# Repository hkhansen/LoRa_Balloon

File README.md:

# LoRa_Balloon
This repository contains all files used for creating and developing the Long Range Tracker balloon tracker.
These trackers are cuurently used by DTU Space for tracking stratospheric balloons carrying experiments.

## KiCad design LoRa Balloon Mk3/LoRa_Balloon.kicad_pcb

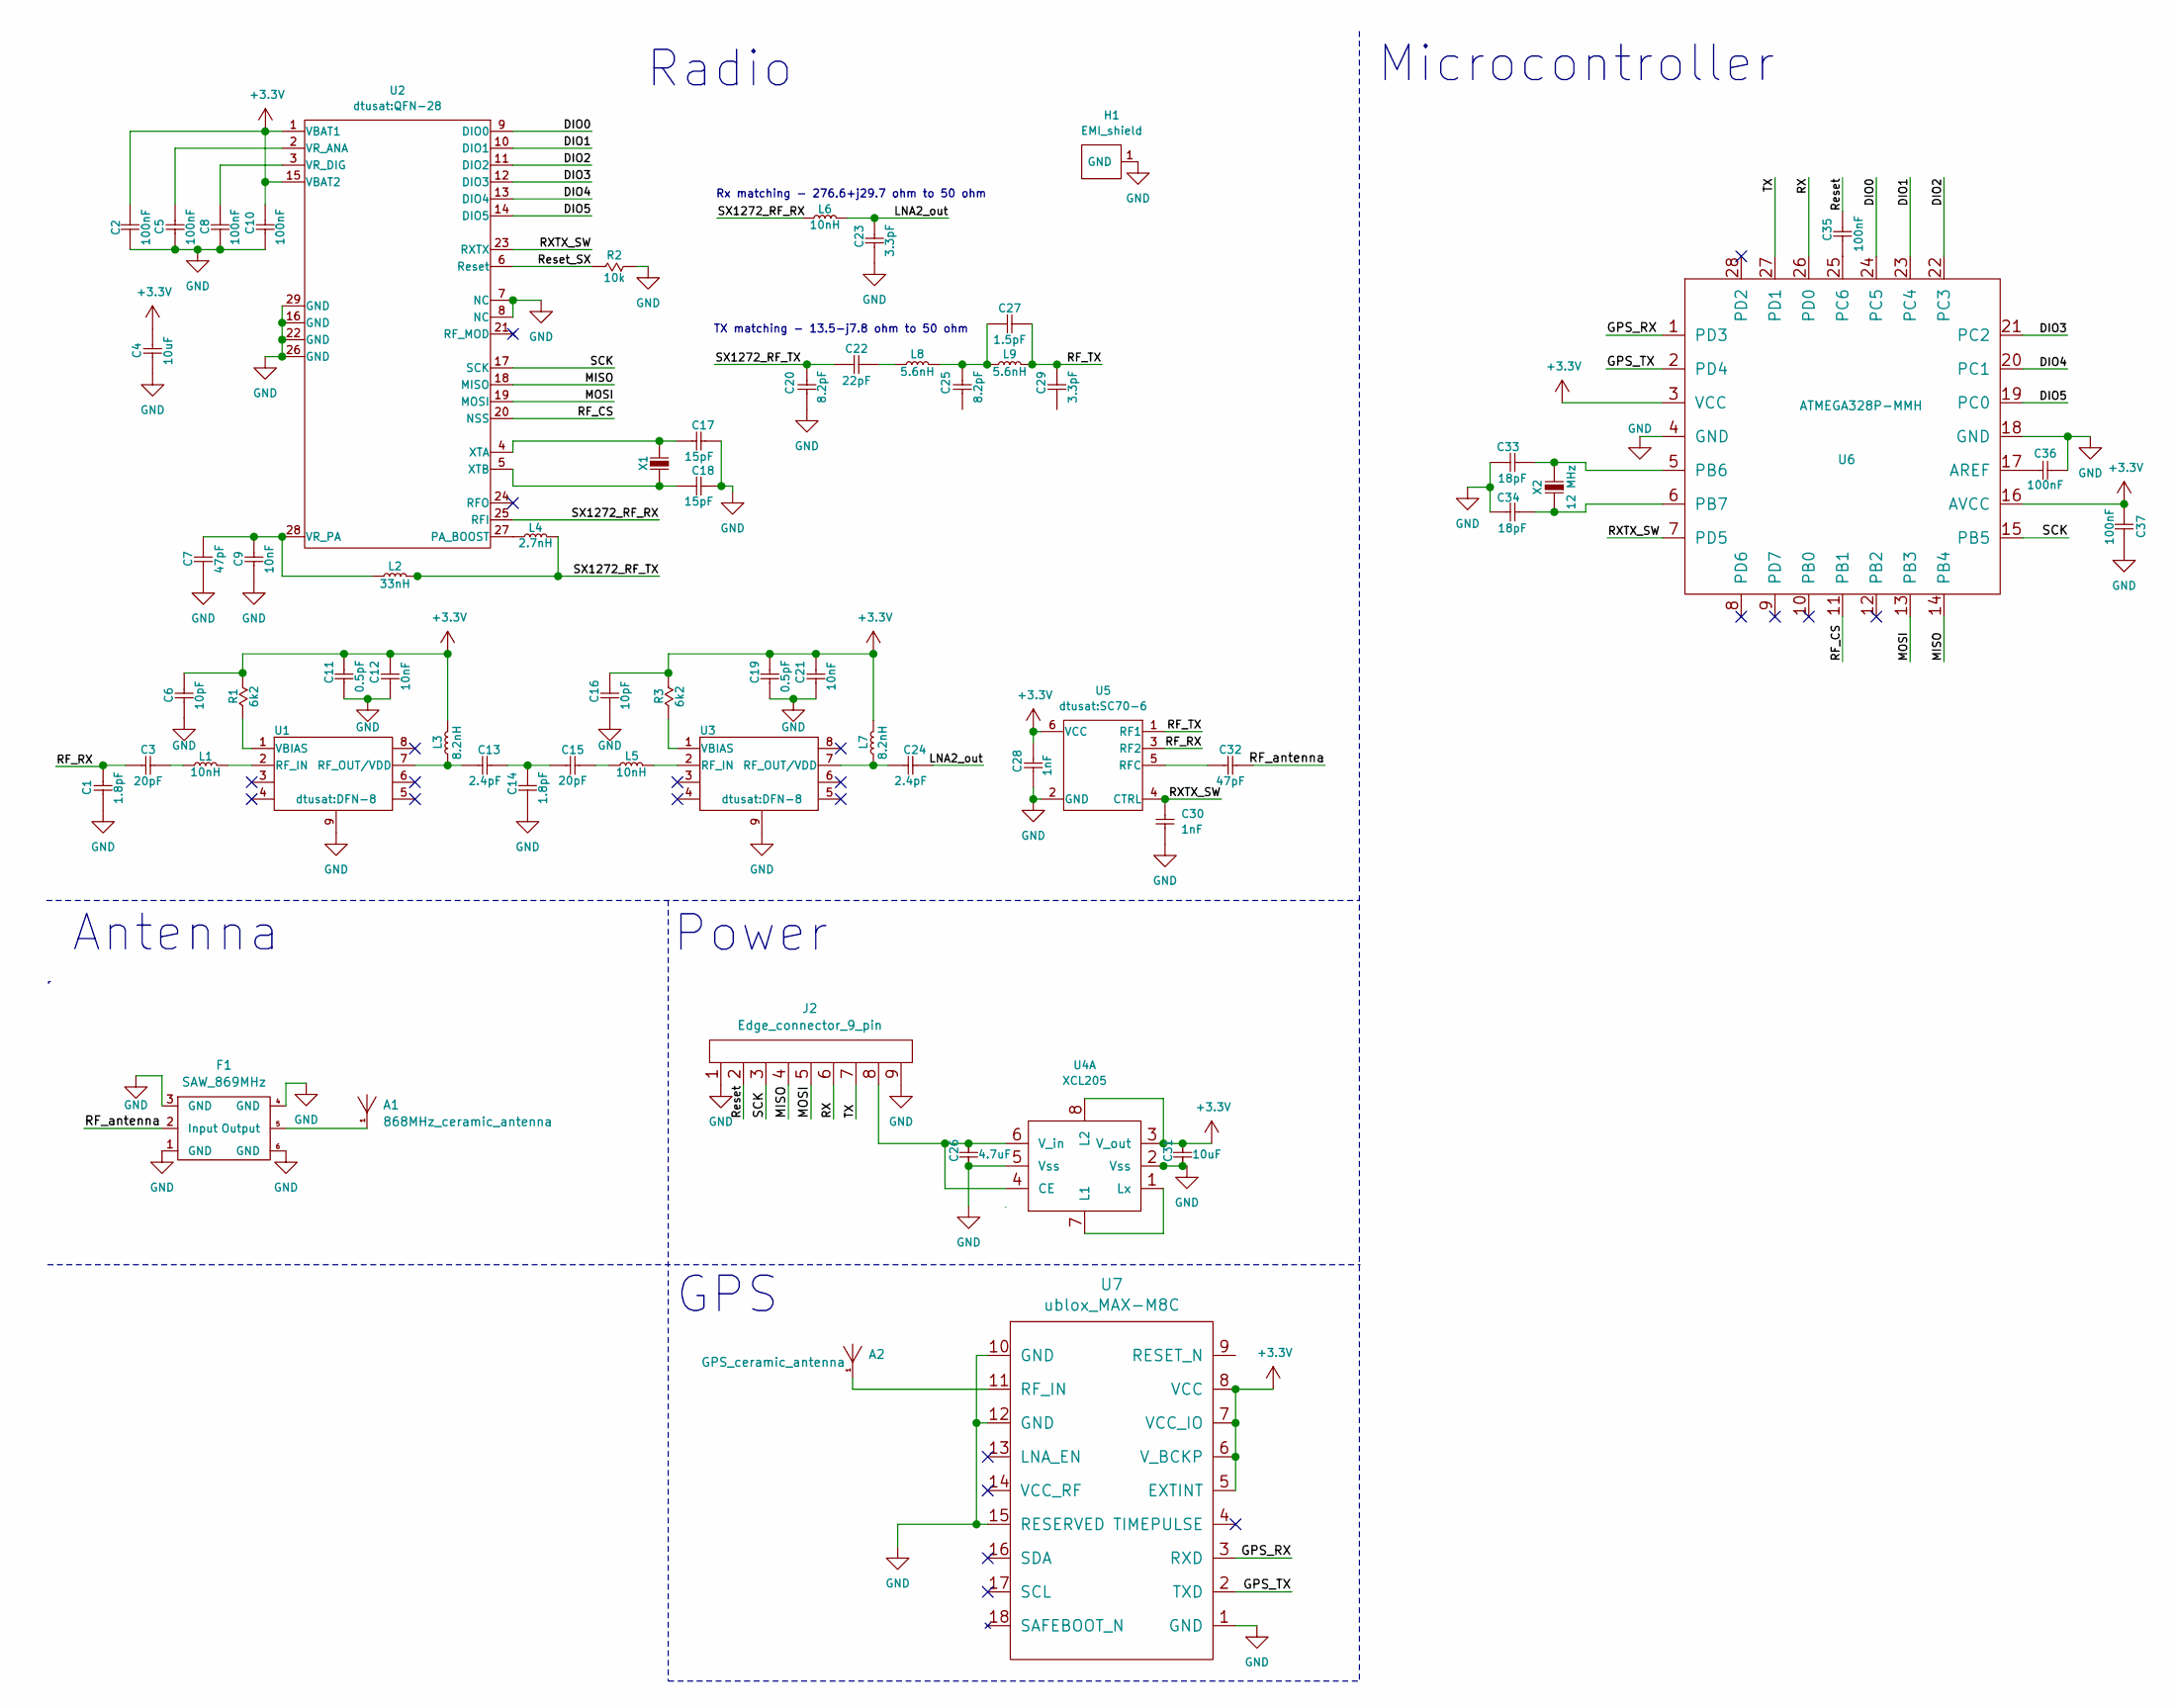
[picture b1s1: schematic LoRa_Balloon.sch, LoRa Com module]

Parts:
A1: 868MHz_ceramic_antenna; Antenna_868MHz
A2: GPS_ceramic_antenna; Ceramic_Antenna
C1, C14: C_0402_1.8pF_CID2085; C0402; Tolerance 0.1pF
C2, C5, C8, C10: C_0402_100nF_CID2080; C0402; Tolerance 10%
C3, C15: C_0402_20pF_CID2086; C0402; Tolerance 5%
C4: C_0805_10uF_CID2079; C0805; Tolerance 10%
C6, C16: C_0402_10pF_CID2089; C0402; Tolerance 1%
C7, C32: C_0402_47pF_CID2081; C0402; Tolerance 5%
C9, C12, C21: C_0402_10nF_CID2082; C0402; Tolerance 10%
C11, C19: C_0402_0.5pF_CID2091; C0402; Tolerance 0.1pF
C13, C24: C_0402_2.4pF_CID2093; C0402; Tolerance 0.05pF
C17, C18: C_0402_15pF_CID2083; C0402; Tolerance 1%
C20, C25: C_0402_8.2pF_CID2088; C0402; Tolerance 0.25pF
C22: C_0402_22pF_CID2090; C0402; Tolerance 5%
C23, C29: C_0402_3.3pF_CID2084; C0402; Tolerance 0.25pF
C26, C31: C_1206_4.7uF_CID2013_small; C0603
C27: C_0402_1.5pF_CID2087; C0402; Tolerance 0.1pF
C28, C30: C_0402_1nF_CID2092; C0402; Tolerance 1%
C33, C34: C_0603_18pF_CID2019; C0402; Tolerance 5%
C35, C36, C37: C_0402_100nF_CID2072; C0402; Tolerance 10%
F1: SAW_869MHz
H1: EMI_shield; BMI-S-203-F_EMI_shield
J2: Edge_connector_9_pin
L1, L5, L6: L_0402_10nH_CID3037; L0402; Tolerance 2%
L2: L_0402_33nH_CID3034; L0402; Tolerance 2nH
L3, L7: L_0402_8.2nH_CID3038; L0402; Tolerance 2%
L4: L_0402_2.7nH_CID3035; L0402; Tolerance 0.1nH
L8, L9: L_0402_5.6nH_CID3036; L0402; Tolerance 0.2nH
R1, R3: R_0402_6k2_CID1104; R0402; Tolerance 1%
R2: R_0402_10k_CID1101; R0402; Tolerance 1%
U1, U3: SKY67013-396LF_CID141; DFN-8
U2: SX1272IMLTRICT-ND_CID104; QFN-28
U4: XCL205
U5: PE4259_CID105; SC70-6
U6: ATMEGA328P-MMH; ATMega328P_MMH
U7: ublox_MAX-M8C
X1: X1E0000210162_CID142; TSX-3225
X2: 7A-12.000MAAJ-T_CID117; TXC14.3

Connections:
+3V3: C4.1, C6.1, C11.1, C12.1, C16.1, C19.1, C21.1, C28.1, C31.1, C37.2, L3.1, L7.1, R1.1, R3.1, U4.3 (V_out), U4.8 (L2), U5.6 (VCC), U6.3 (VCC), U6.16 (AVCC), U7.5 (EXTINT), U7.6 (V_BCKP), U7.7 (VCC_IO), U7.8 (VCC)
/DIO0: U2.9 (DIO0), U6.24 (PC5)
/DIO1: U2.10 (DIO1), U6.23 (PC4)
/DIO2: U2.11 (DIO2), U6.22 (PC3)
/DIO3: U2.12 (DIO3), U6.21 (PC2)
/DIO4: U2.13 (DIO4), U6.20 (PC1)
/DIO5: U2.14 (DIO5), U6.19 (PC0)
/GPS_RX: U6.1 (PD3), U7.3 (RXD)
/GPS_TX: U6.2 (PD4), U7.2 (TXD)
/LNA2_out: C23.1, C24.1, L6.1
/MISO: J2.4, U2.18 (MISO), U6.14 (PB4)
/MOSI: J2.5, U2.19 (MOSI), U6.13 (PB3)
/RF_CS: U2.20 (NSS), U6.11 (PB1)
/RF_RX: C1.1, C3.2, U5.3 (RF2)
/RF_TX: C27.1, C29.1, L9.1, U5.1 (RF1)
/RF_antenna: C32.1, F1.2 (Input)
/RX: J2.6, U6.26 (PD0)
/RXTX_SW: C30.1, U2.23 (RXTX), U5.4 (CTRL), U6.7 (PD5)
/Reset: C35.1, J2.2
/Reset_SX: R2.2, U2.6 (Reset)
/SCK: J2.3, U2.17 (SCK), U6.15 (PB5)
/SX1272_RF_RX: L6.2, U2.25 (RFI)
/SX1272_RF_TX: C20.1, C22.2, L2.1, L4.1
/TX: J2.7, U6.27 (PD1)
GND: C1.2, C2.2, C4.2, C5.2, C6.2, C7.2, C8.2, C9.2, C10.2, C11.2, C12.2, C14.2, C16.2, C17.1, C18.1, C19.2, C20.2, C21.2, C23.2, C26.2, C28.2, C30.2, C31.2, C33.1, C34.1, C36.1, C37.1, F1.1 (GND), F1.3 (GND), F1.4 (GND), F1.6 (GND), H1.1, J2.1, J2.9, R2.1, U1.9, U2.7 (NC), U2.8 (NC), U2.16 (GND), U2.22 (GND), U2.26 (GND), U2.29 (GND), U3.9, U4.2 (Vss), U4.5 (Vss), U4.GND, U5.2 (GND), U6.4 (GND), U6.18 (GND), U7.1 (GND), U7.10 (GND), U7.12 (GND), U7.15 (RESERVED)
unnamed: A1.1, F1.5 (Output)
unnamed: A2.1, U7.11 (RF_IN)
unnamed: C3.1, L1.2
unnamed: C5.1, U2.2 (VR_ANA)
unnamed: C7.1, C9.1, L2.2, U2.28 (VR_PA)
unnamed: C8.1, U2.3 (VR_DIG)
unnamed: C2.1, C10.1, U2.1 (VBAT1), U2.15 (VBAT2)
unnamed: C13.1, C14.1, C15.2
unnamed: C13.2, L3.2, U1.7 (RF_OUT/VDD)
unnamed: C15.1, L5.2
unnamed: C17.2, U2.4 (XTA), X1.1
unnamed: C18.2, U2.5 (XTB), X1.3
unnamed: C22.1, L8.2
unnamed: C24.2, L7.2, U3.7 (RF_OUT/VDD)
unnamed: C25.1, C27.2, L8.1, L9.2
unnamed: C26.1, J2.8, U4.4 (CE), U4.6 (V_in)
unnamed: C32.2, U5.5 (RFC)
unnamed: C33.2, U6.5 (PB6), X2.2
unnamed: C34.2, U6.6 (PB7), X2.1
unnamed: C35.2, U6.25 (PC6)
unnamed: C36.2, U6.17 (AREF)
unnamed: L1.1, U1.2 (RF_IN)
unnamed: L4.2, U2.27 (PA_BOOST)
unnamed: L5.1, U3.2 (RF_IN)
unnamed: R1.2, U1.1 (VBIAS)
unnamed: R3.2, U3.1 (VBIAS)
unnamed: U4.1 (Lx), U4.7 (L1)

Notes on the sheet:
Rx matching - 276.6+j29.7 ohm to 50 ohm
TX matching - 13.5-j7.8 ohm to 50 ohm
Radio
Antenna
Power
Microcontroller
GPS

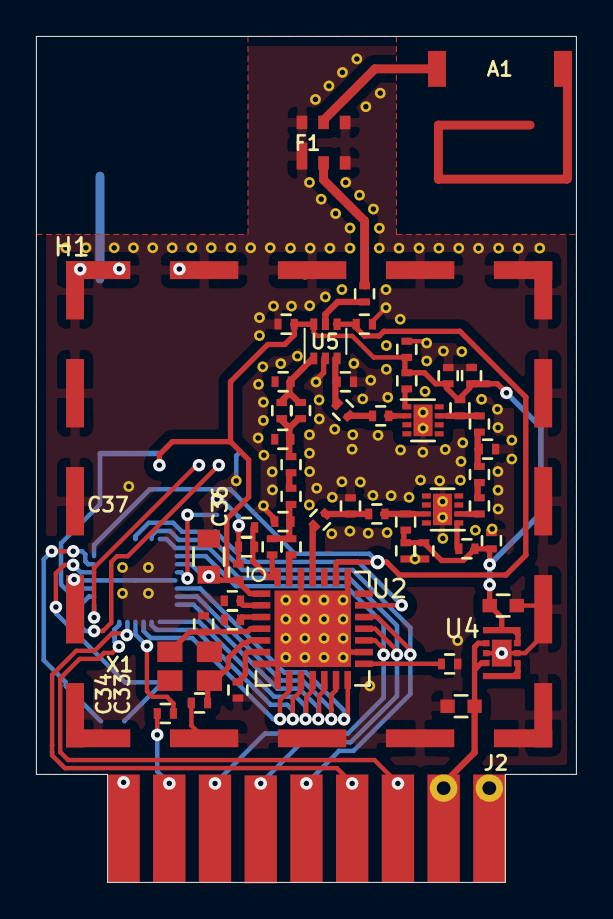
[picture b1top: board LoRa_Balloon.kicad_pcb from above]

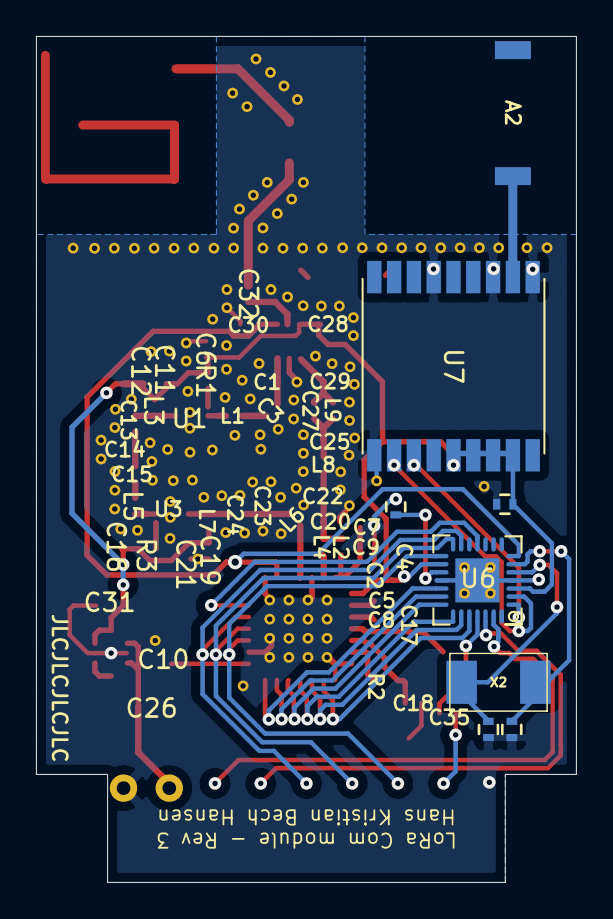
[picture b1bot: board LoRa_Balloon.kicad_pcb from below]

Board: 2 copper layers, 30.0 x 47.0 mm, 63 parts (8 on the bottom side), 52 nets.

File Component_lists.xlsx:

Componet references - LoRa_Balloon
Capacitors
REF | Value | Unit | CID
C1, C14 | 1.8 | pF | 2085
C11, C19 | 0.5 | pF | 2091
C13, C24 | 2.4 | pF | 2093
C17, C18 | 15 | pF | 2083
C2, C5, C8, C10, C33, C34, C35, C36 | 100 | nF | 2080
C20, C25 | 8.1999999999999993 | pF | 2088
C22 | 22 | pF | 2090
C23, C28 | 3.3 | pF | 2084
C26 | 1.5 | pF | 2087
C27, C29 | 1 | nF | 2092
C3, C15 | 20 | pF | 2086
C31, C32 | 18 | pF | 2019
C37 | 4.7 | uF | 2013
C4, C12 | 10 | uF | 2079
C7, C30, C38 | 47 | pF | 2081
C6, C16 | 10 | pF | 2089
C9, C21 | 10 | nF | 2082

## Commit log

2019-12-10 Updated schematic
2019-12-11 Schematics finished
2019-12-12 Added libary to repository
2019-12-12 PCB finished
2019-12-13 Rearranged component labels
2019-12-16 New folder structure - more versions
2019-12-19 New FR4 versions
2020-01-13 Changed names
2020-01-13 Added mk1 enclosure
2020-01-14 Update to 3D
2020-01-14 Finished all 3D designs
2020-01-15 Removed unused versions
2020-01-15 Added other versions of 3D
2020-01-16 Created STL-files
2020-01-21 Small fixes to Mk2.1
2020-02-03 Updated spreadsheet with components
2022-07-02 Updated libraries
2022-07-23 Created battery box model
2022-08-29 Mk 3 created
2022-08-29 Footprint and symbol for GPS chip
2022-08-29 Created and added new component STEP files
2022-08-31 Added Firmware to repo
2022-09-05 Finished board layout
2022-09-13 Added holes for battery connection
2023-01-05 Mk3 enclosure created
2023-01-06 Updated Mk3 enclosure lid
